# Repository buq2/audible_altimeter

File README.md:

# audible_altimeter

KiCad schematics for electronic skydiving altimeter.

More information at http://buq2.com/

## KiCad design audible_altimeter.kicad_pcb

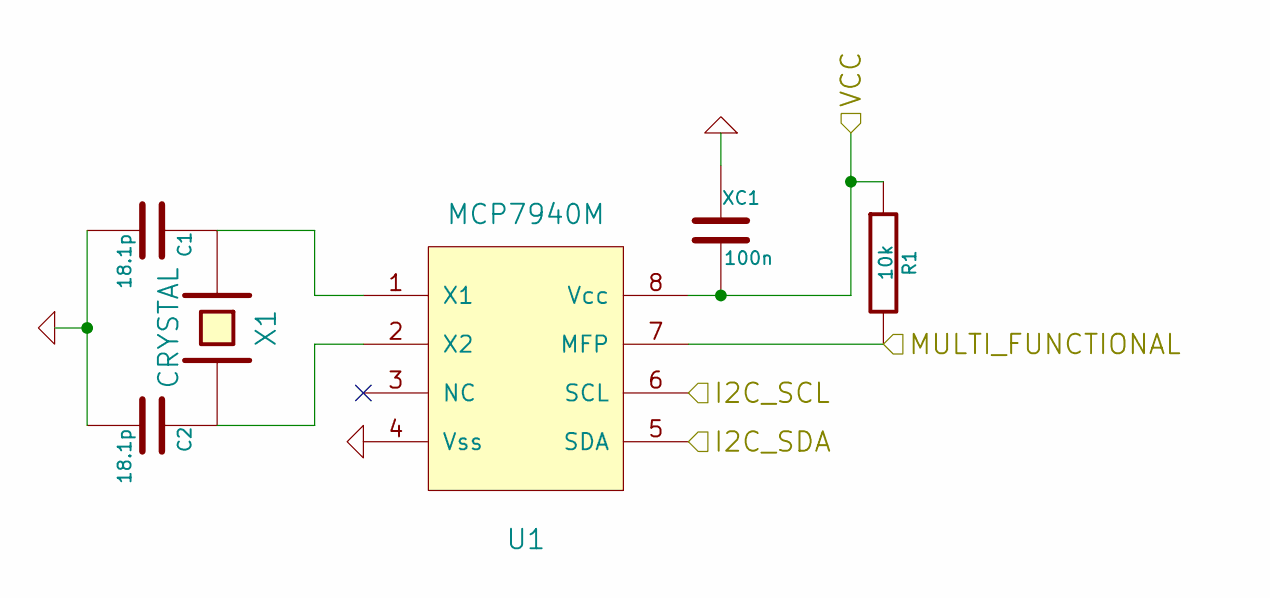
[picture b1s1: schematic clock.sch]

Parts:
C1, C2: 18.1p; SM0603
R1: 10k; SM0603
U1: MCP7940M; 8-TDFN
X1: CRYSTAL; SM0805
XC1: 100n; SM0603

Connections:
/Barometer/I2C_SCL: U1.6 (SCL); also elsewhere on the board
/Barometer/I2C_SDA: U1.5 (SDA); also elsewhere on the board
/Battery/+3.3V: R1.1, U1.8 (Vcc), XC1.2; also elsewhere on the board
/MCU/CLOCK_INT: R1.2, U1.7 (MFP); also elsewhere on the board
GND: C1.2, C2.2, U1.4 (Vss), XC1.1; also elsewhere on the board
unnamed: C1.1, U1.1 (X1), X1.1
unnamed: C2.1, U1.2 (X2), X1.2

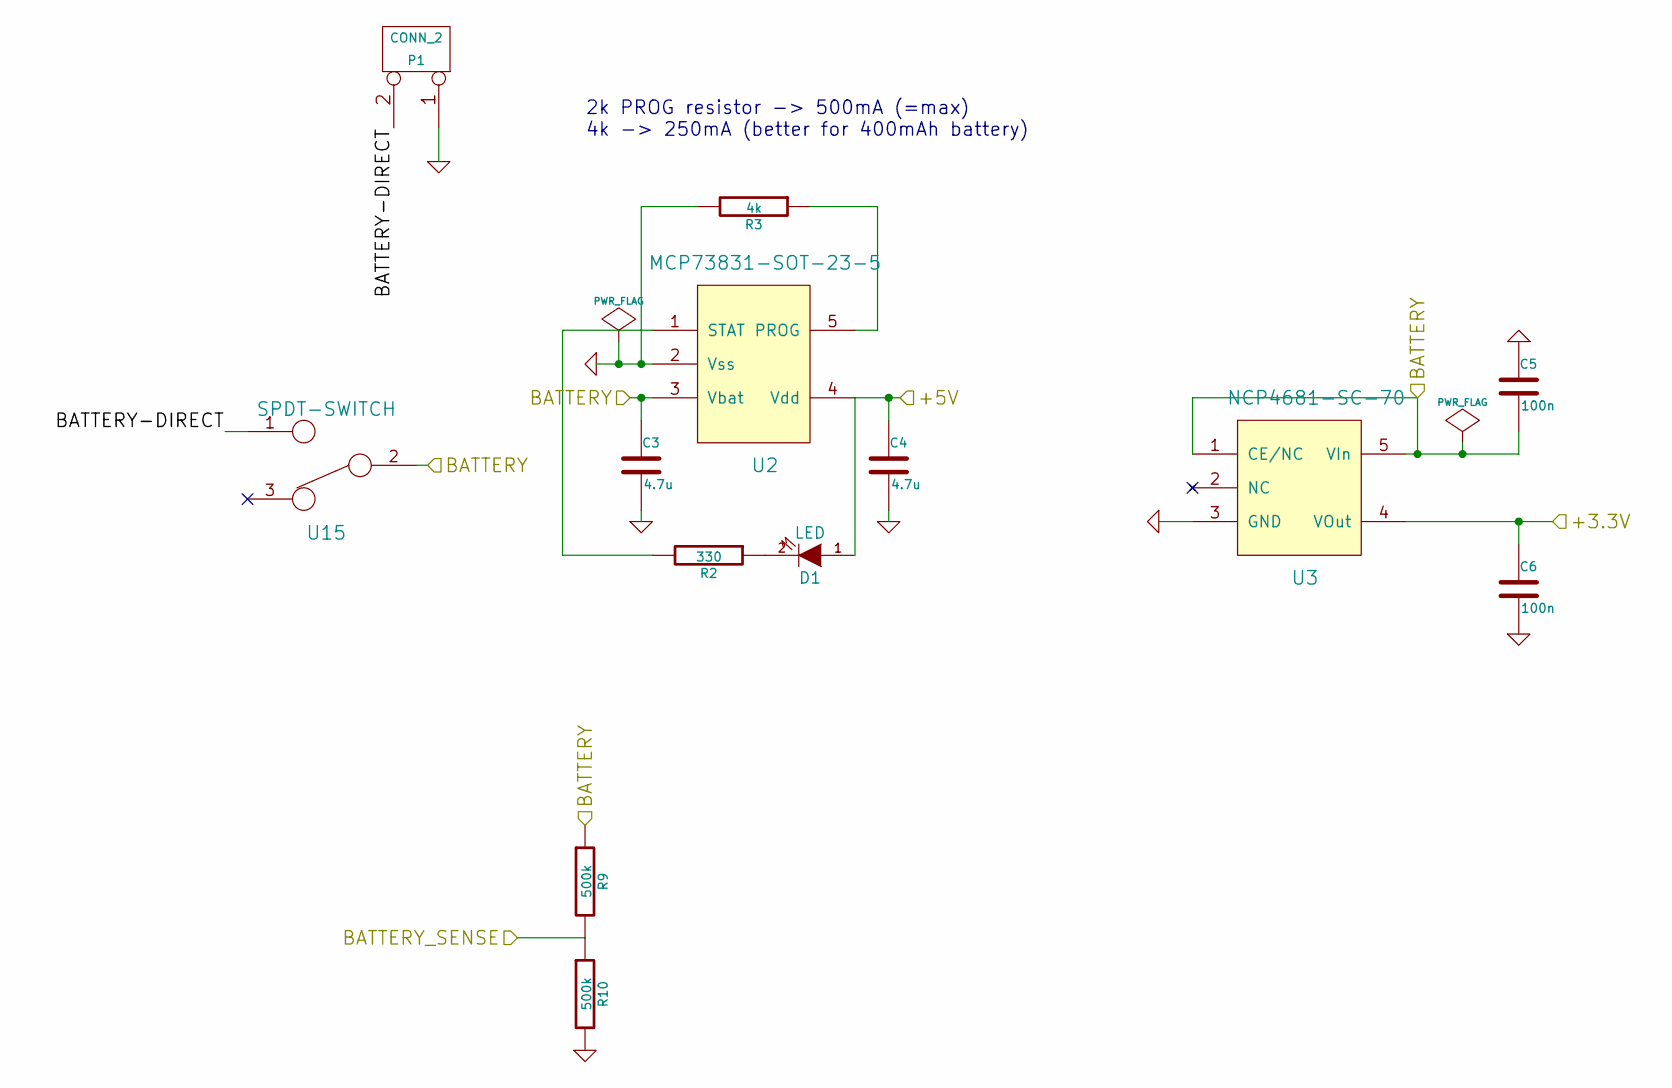
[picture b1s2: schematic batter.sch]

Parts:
C3, C4: 4.7u; SM0805
C5, C6: 100n; SM0603
D1: LED; SM0603
P1: CONN_2; PIN_HEADER_2
R2: 330; SM0603
R3: 4k; SM0603
R9, R10: 500k; SM0603
U2: MCP73831-SOT-23-5; SOT-23-5
U3: NCP4681-SC-70; SOT-353
U15: SPDT-SWITCH; CUS-12TB-SWITCH

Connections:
/Battery/+3.3V: C6.1, U3.4 (VOut); also elsewhere on the board
/Battery/+5V: C4.1, D1.1 (A), U2.4 (Vdd); also elsewhere on the board
/Battery/BATTERY: C3.1, C5.2, R9.1, U2.3 (Vbat), U3.1 (CE/NC), U3.5 (VIn), U15.2; also elsewhere on the board
/Battery/BATTERY-DIRECT: P1.2 (PM), U15.1
/Battery/BATTERY_SENSE: R9.2, R10.1; also elsewhere on the board
GND: C3.2, C4.2, C5.1, C6.2, P1.1, R3.2, R10.2, U2.2 (Vss), U3.3 (GND); also elsewhere on the board
unnamed: D1.2 (K), R2.1
unnamed: R2.2, U2.1 (STAT)
unnamed: R3.1, U2.5 (PROG)

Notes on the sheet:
2k PROG resistor -> 500mA (=max) 4k -> 250mA (better for 400mAh battery)

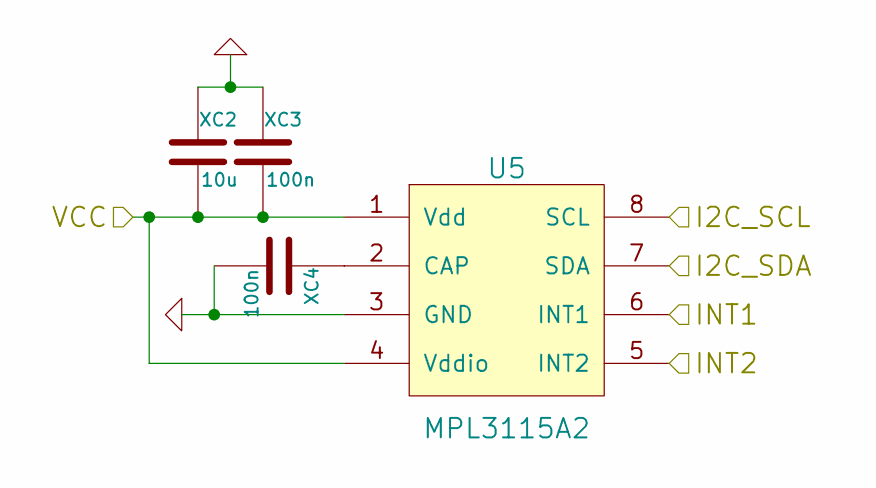
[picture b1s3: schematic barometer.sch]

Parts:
U5: MPL3115A2; 8-TLGA
XC2: 10u; SM0805
XC3, XC4: 100n; SM0603

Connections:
/Barometer/I2C_SCL: U5.8 (SCL); also elsewhere on the board
/Barometer/I2C_SDA: U5.7 (SDA); also elsewhere on the board
/Battery/+3.3V: U5.1 (Vdd), U5.4 (Vddio), XC2.2, XC3.2; also elsewhere on the board
/MCU/BAROMETER_INT: U5.6 (INT1); also elsewhere on the board
GND: U5.3 (GND), XC2.1, XC3.1, XC4.2; also elsewhere on the board
unnamed: U5.2 (CAP), XC4.1

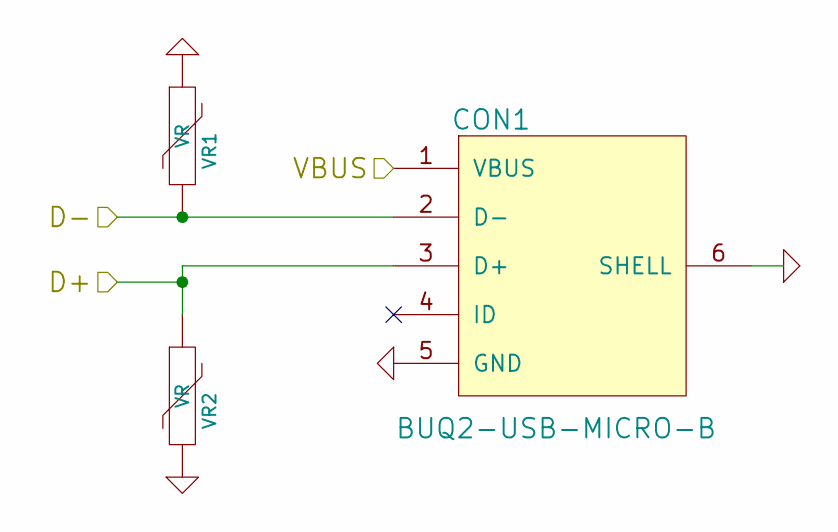
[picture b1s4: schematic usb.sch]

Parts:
CON1: BUQ2-USB-MICRO-B; USB-MICRO-B-FCI-10118194; Digikey 609-4616-1-ND
VR1, VR2: VR; SM0603

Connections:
/Battery/+5V: CON1.1 (VBUS); also elsewhere on the board
/MCU/D+: CON1.3 (D+), VR2.1; also elsewhere on the board
/MCU/D-: CON1.2 (D-), VR1.2; also elsewhere on the board
GND: CON1.5 (GND), CON1.6 (SHELL), VR1.1, VR2.2; also elsewhere on the board

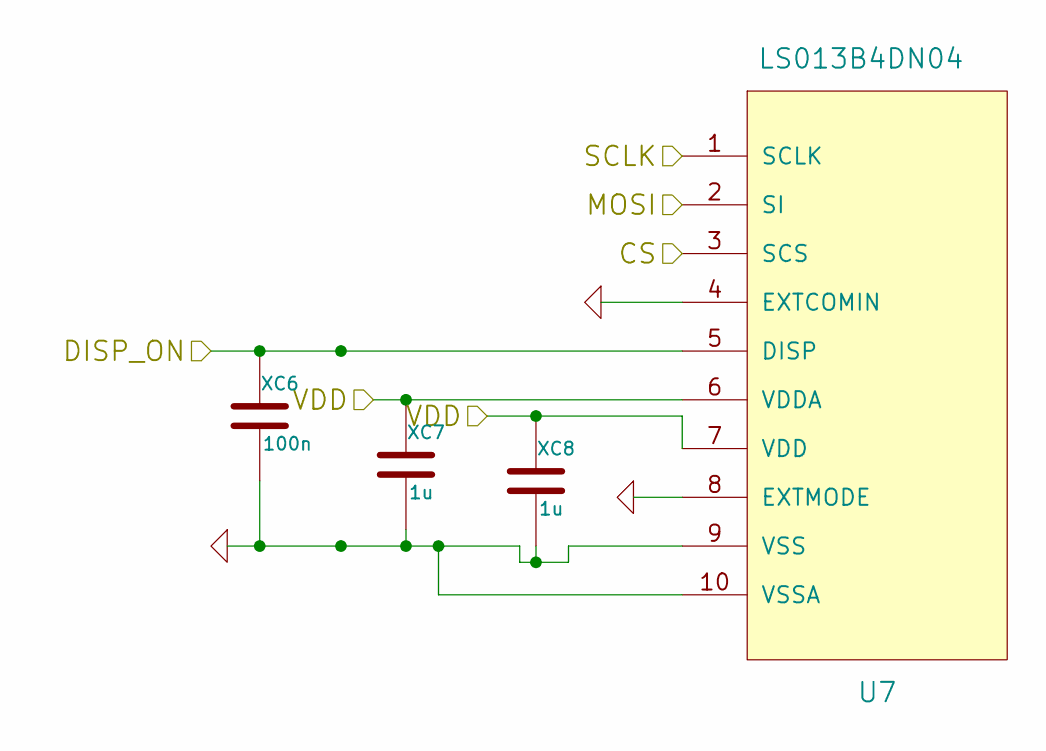
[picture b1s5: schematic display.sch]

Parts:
U7: LS013B4DN04; FPC-CONN-10-FCI-TOP-CONTACTS
XC6: 100n; SM0603
XC7, XC8: 1u; SM0603

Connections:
/Battery/+3.3V: U7.6 (VDDA), U7.7 (VDD), XC7.1, XC8.1; also elsewhere on the board
/Display/CS: U7.3 (SCS); also elsewhere on the board
/Display/DISP_ON: U7.5 (DISP), XC6.1; also elsewhere on the board
/Display/MOSI: U7.2 (SI); also elsewhere on the board
/MCU/SCK: U7.1 (SCLK); also elsewhere on the board
GND: U7.4 (EXTCOMIN), U7.8 (EXTMODE), U7.9 (VSS), U7.10 (VSSA), XC6.2, XC7.2, XC8.2; also elsewhere on the board

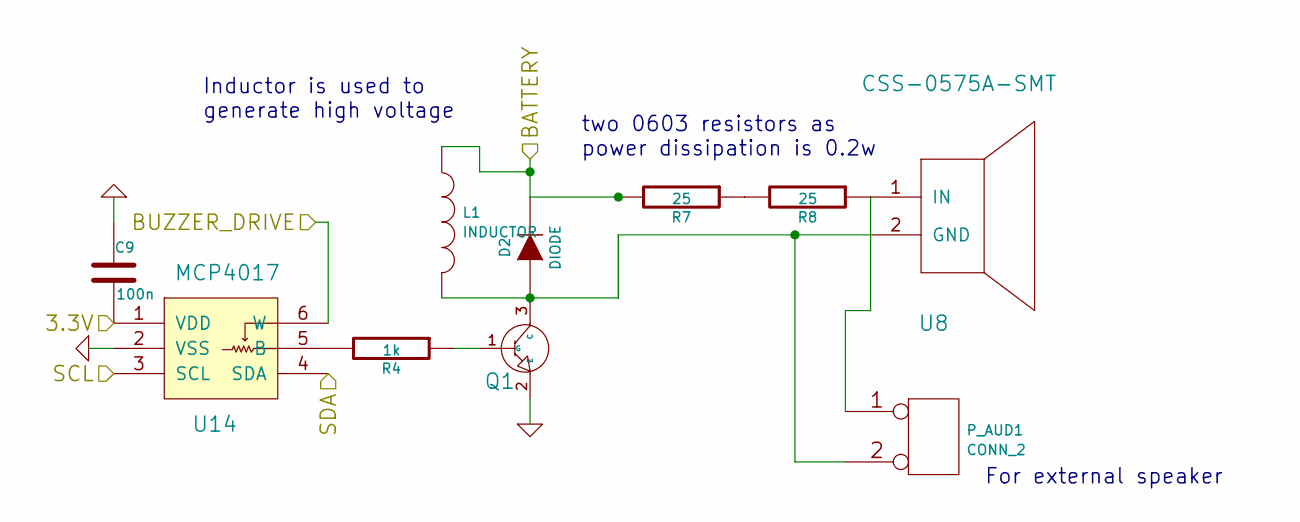
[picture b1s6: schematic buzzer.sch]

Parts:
C9: 100n; SM0603
D2: DIODE; SM0603
L1: INDUCTOR
P_AUD1: CONN_2
Q1: NPN-SOT23; SOT-23-3
R4: 1k; SM0603
R7, R8: 25; SM0603
U8: CSS-0575A-SMT; BUZZER-CUI-5MM
U14: MCP4017; SC-70-6

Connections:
/Barometer/I2C_SCL: U14.3 (SCL); also elsewhere on the board
/Barometer/I2C_SDA: U14.4 (SDA); also elsewhere on the board
/Battery/+3.3V: C9.2, U14.1 (VDD); also elsewhere on the board
/Battery/BATTERY: D2.2 (K), L1.1, R7.2; also elsewhere on the board
/Buzzer/BUZZER_DRIVE: U14.6 (W); also elsewhere on the board
GND: C9.1, Q1.2 (E), U14.2 (VSS); also elsewhere on the board
unnamed: D2.1 (A), L1.2, P_AUD1.2 (PM), Q1.3 (C), U8.2 (GND)
unnamed: Q1.1 (G), R4.1
unnamed: R4.2, U14.5 (B)
unnamed: R7.1, R8.2
unnamed: P_AUD1.1, R8.1, U8.1 (IN)

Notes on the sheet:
two 0603 resistors as power dissipation is 0.2w
For external speaker
Inductor is used to generate high voltage

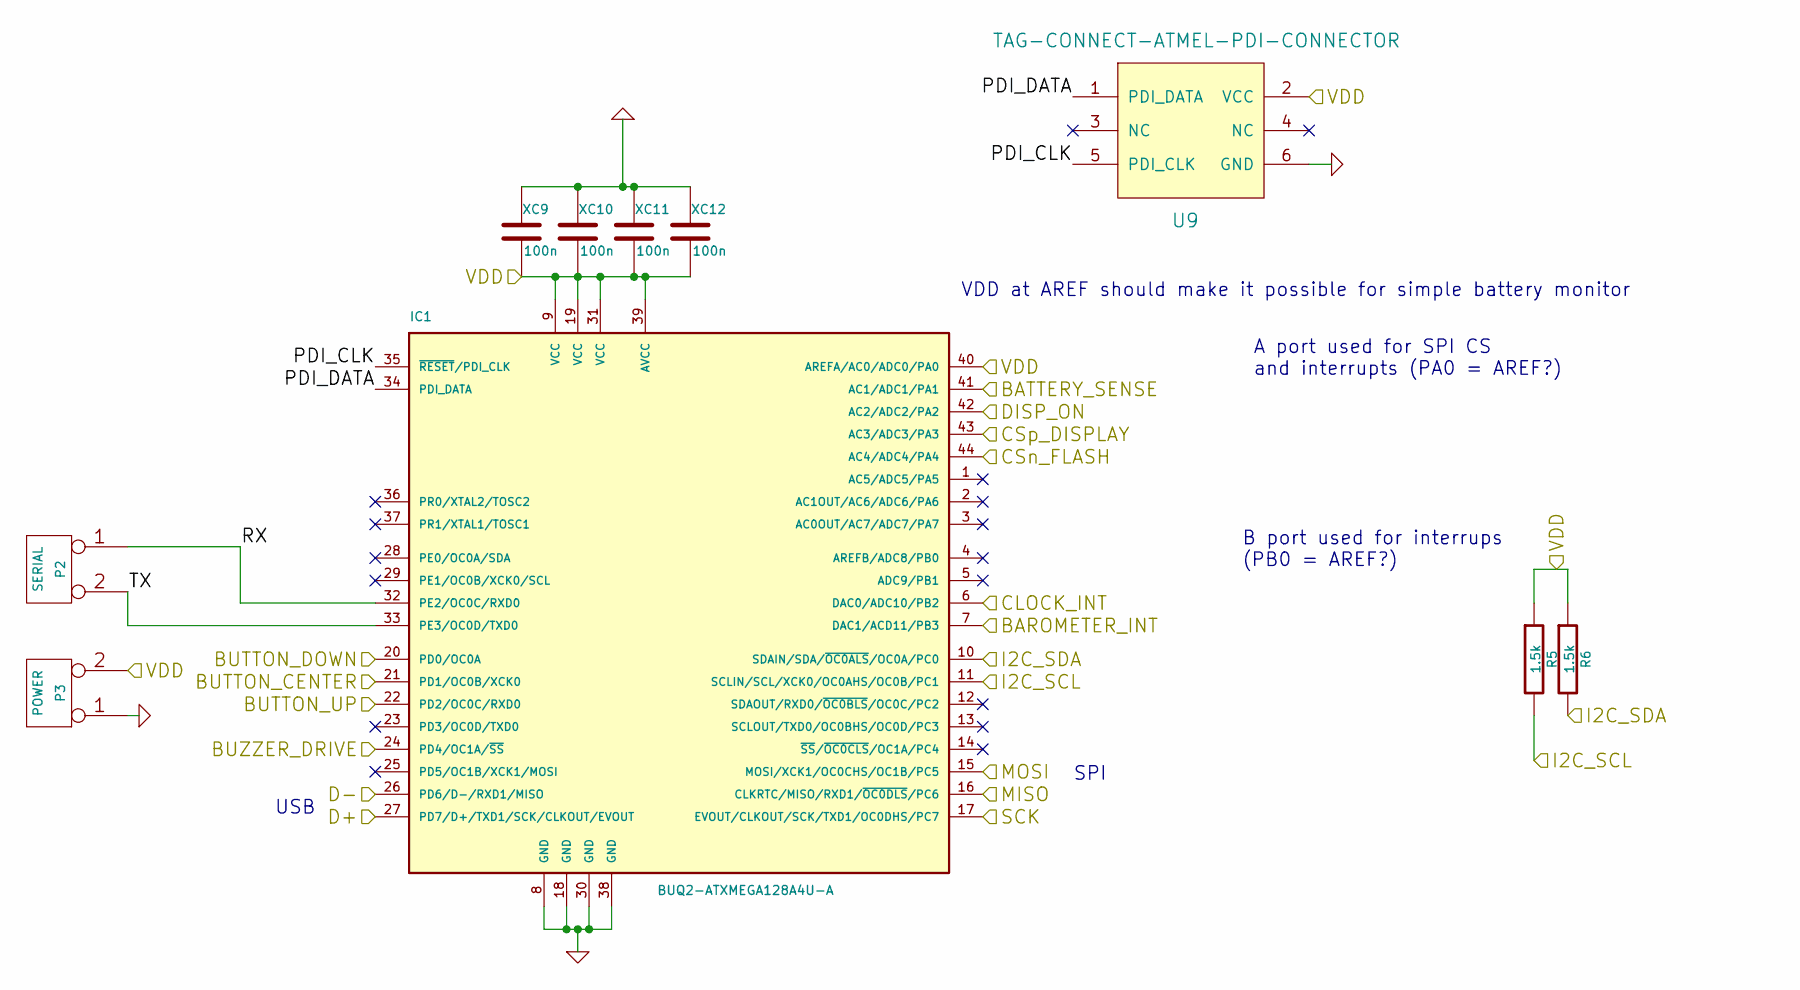
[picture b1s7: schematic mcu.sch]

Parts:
IC1: BUQ2-ATXMEGA128A4U-A; BUQ2-TQFP44
P2: SERIAL; PIN_HEADER_2
P3: POWER; PIN_HEADER_2
R5, R6: 1.5k; SM0603
U9: TAG-CONNECT-ATMEL-PDI-CONNECTOR; TAG-CONNECT6
XC9, XC10, XC11, XC12: 100n; SM0603

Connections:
/Barometer/I2C_SCL: IC1.11 (SCLIN/SCL/XCK0/OC0AHS/OC0B/PC1), R5.2; also elsewhere on the board
/Barometer/I2C_SDA: IC1.10 (SDAIN/SDA/~OC0ALS~/OC0A/PC0), R6.2; also elsewhere on the board
/Battery/+3.3V: IC1.9 (VCC), IC1.19 (VCC), IC1.31 (VCC), IC1.39 (AVCC), IC1.40 (AREFA/AC0/ADC0/PA0), P3.2 (PM), R5.1, R6.1, U9.2 (VCC), XC9.2, XC10.2, XC11.2, XC12.2; also elsewhere on the board
/Battery/BATTERY_SENSE: IC1.41 (AC1/ADC1/PA1); also elsewhere on the board
/Buttons/BUTTON_CENTER: IC1.21 (PD1/OC0B/XCK0); also elsewhere on the board
/Buttons/BUTTON_DOWN: IC1.20 (PD0/OC0A); also elsewhere on the board
/Buttons/BUTTON_UP: IC1.22 (PD2/OC0C/RXD0); also elsewhere on the board
/Buzzer/BUZZER_DRIVE: IC1.24 (PD4/OC1A/~SS~); also elsewhere on the board
/Display/CS: IC1.43 (AC3/ADC3/PA3); also elsewhere on the board
/Display/DISP_ON: IC1.42 (AC2/ADC2/PA2); also elsewhere on the board
/Display/MOSI: IC1.15 (MOSI/XCK1/OC0CHS/OC1B/PC5); also elsewhere on the board
/MCU/BAROMETER_INT: IC1.7 (DAC1/ACD11/PB3); also elsewhere on the board
/MCU/CLOCK_INT: IC1.6 (DAC0/ADC10/PB2); also elsewhere on the board
/MCU/CSn_FLASH: IC1.44 (AC4/ADC4/PA4); also elsewhere on the board
/MCU/D+: IC1.27 (PD7/D+/TXD1/SCK/CLKOUT/EVOUT); also elsewhere on the board
/MCU/D-: IC1.26 (PD6/D-/RXD1/MISO); also elsewhere on the board
/MCU/MISO: IC1.16 (CLKRTC/MISO/RXD1/~OC0DLS~/PC6); also elsewhere on the board
/MCU/PDI_CLK: IC1.35 (~RESET~/PDI_CLK), U9.5 (PDI_CLK)
/MCU/PDI_DATA: IC1.34 (PDI_DATA), U9.1 (PDI_DATA)
/MCU/RX: IC1.32 (PE2/OC0C/RXD0), P2.1
/MCU/SCK: IC1.17 (EVOUT/CLKOUT/SCK/TXD1/OC0DHS/PC7); also elsewhere on the board
/MCU/TX: IC1.33 (PE3/OC0D/TXD0), P2.2 (PM)
GND: IC1.8 (GND), IC1.18 (GND), IC1.30 (GND), IC1.38 (GND), P3.1, U9.6 (GND), XC9.1, XC10.1, XC11.1, XC12.1; also elsewhere on the board

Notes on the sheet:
SPI
USB
A port used for SPI CS and interrupts (PA0 = AREF?)
B port used for interrups (PB0 = AREF?)
VDD at AREF should make it possible for simple battery monitor

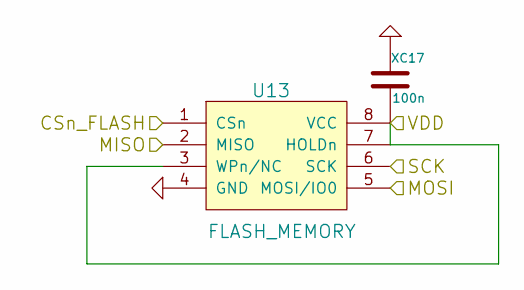
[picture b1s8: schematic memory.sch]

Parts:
U13: FLASH_MEMORY; 8-SOIC
XC17: 100n; SM0603

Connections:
/Battery/+3.3V: U13.3 (WPn/NC), U13.7 (HOLDn), U13.8 (VCC), XC17.2; also elsewhere on the board
/Display/MOSI: U13.5 (MOSI/IO0); also elsewhere on the board
/MCU/CSn_FLASH: U13.1 (CSn); also elsewhere on the board
/MCU/MISO: U13.2 (MISO); also elsewhere on the board
/MCU/SCK: U13.6 (SCK); also elsewhere on the board
GND: U13.4 (GND), XC17.1; also elsewhere on the board

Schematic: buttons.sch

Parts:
U4: UP; PUSHBUTTON_4x4_5x5_ROTATED_4_PIN
U10: CNT; PUSHBUTTON_4x4_5x5_ROTATED_4_PIN
U11: DWN; PUSHBUTTON_4x4_5x5_ROTATED_4_PIN

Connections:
/Buttons/BUTTON_CENTER: U10.4; also elsewhere on the board
/Buttons/BUTTON_DOWN: U11.4; also elsewhere on the board
/Buttons/BUTTON_UP: U4.4; also elsewhere on the board
GND: U4.1, U10.1, U11.1; also elsewhere on the board

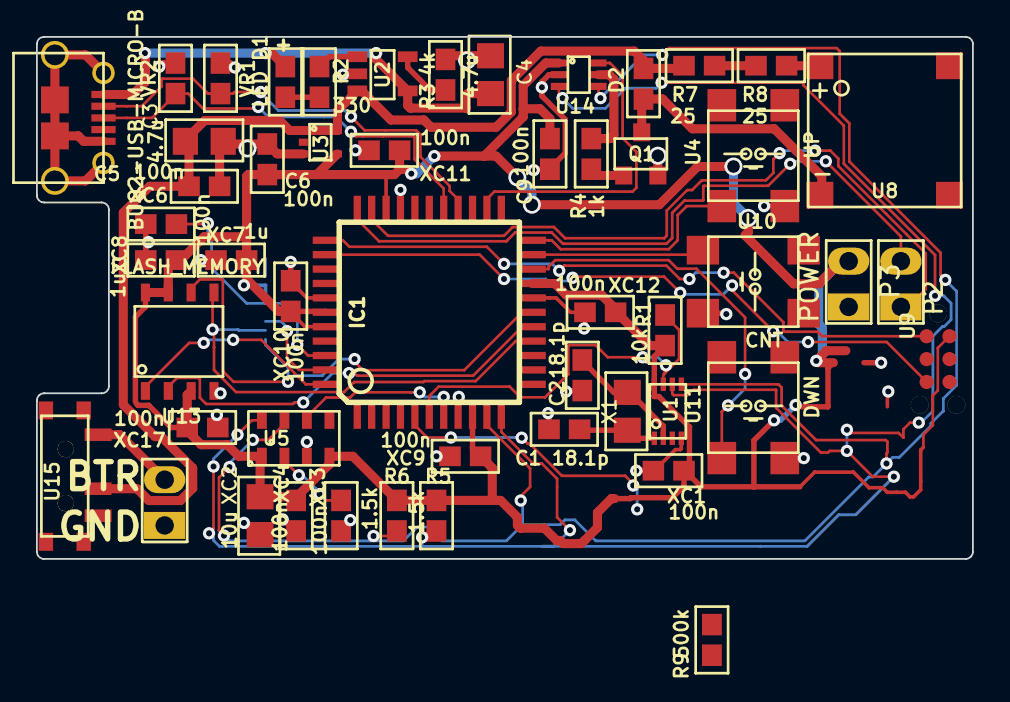
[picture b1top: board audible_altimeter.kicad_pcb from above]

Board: 2 copper layers, 52.0 x 29.0 mm, 52 parts (1 on the bottom side), 37 nets.

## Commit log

2014-10-19 Init
2014-10-19 Component assignements
2014-10-20 Start adding power components
2014-10-21 Assign some components
2014-10-21 Start using hierarchical sheets
2014-11-10 Add gps
2014-11-11 Add humidity sensor
2014-11-11 More connections
2014-11-12 Add flash and ram. Some connections and DRC cleaning
2014-11-12 Add buttons. Fix DRC. Add antenna
2014-11-12 Start first layout test
2014-11-13 Little bit layout
2014-11-15 Some easy routing
2014-11-15 Layouting
2014-11-29 Before making larger board. - Changed GPS module
2014-11-30 Before adding proper reset and battery monitor
2014-11-30 V1 version which was ordered
2015-01-26 Add missing(?) file
2015-01-26 Start planning test board v2.0
2015-01-27 Almost ready routing
2015-01-27 Add new barometer
2015-01-27 Ordered version 2.0 (pcb and stencil)
2015-01-27 Remove deleted schematics
2015-02-03 Case: Before difference
2015-02-03 With 0,1,1.5mm kerf
2015-02-03 Some modifications to the case
2015-02-03 Add readme about the case
2015-02-05 Modify such that the manufacturer accepts the file (formulor.de)
2015-04-15 Start implementing new version: move USB port and altimeter module, new buzzer and volume control
2015-04-17 Before starting laying out tracks
2015-04-18 Continuing laying out tracks
2015-04-18 Ordered v3.0
2015-04-18 Change few footprints to ones with (simple) 3d models
2016-03-05 Some changes?
2018-10-26 Add project image
2022-03-15 Add board images
